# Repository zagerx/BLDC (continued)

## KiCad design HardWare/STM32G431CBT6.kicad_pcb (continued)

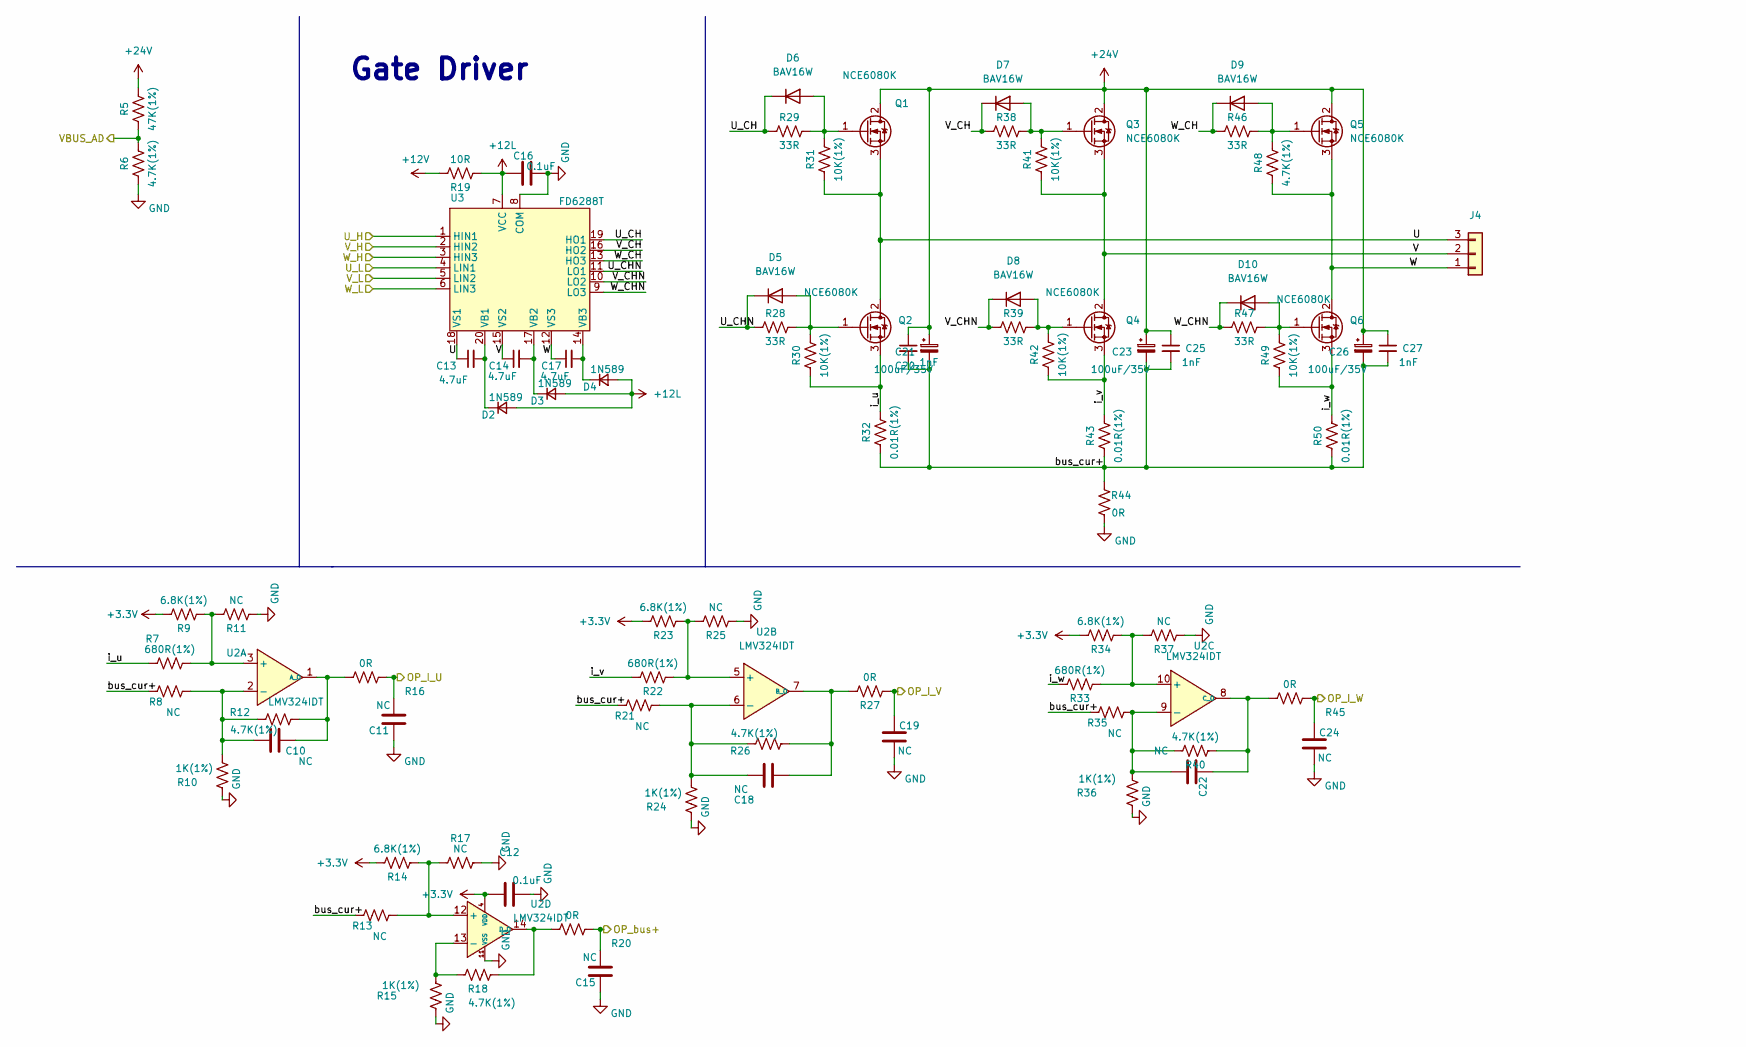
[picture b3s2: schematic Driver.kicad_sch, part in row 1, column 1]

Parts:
C10, C11, C15, C18, C19, C22, C24: NC; C_0603_1608Metric
C12, C16: 0.1uF; C_0603_1608Metric
C13, C14, C17: 4.7uF; C_0805_2012Metric
C20, C25, C27: 1nF; C_0603_1608Metric
C21, C23, C26: 100uF/35V; CP_Radial_D6.3mm_P2.50mm
D2, D3, D4: 1N589; D_SOD-123
D5, D6, D7, D8, D9, D10: BAV16W; D_SOD-123
J4: Conn_01x03; TerminalBlock_bornier-3_P5.08mm
Q1, Q2, Q3, Q4, Q5, Q6: NCE6080K; TO-252-2
R5: 47K(1%); R_0603_1608Metric
R6, R12, R18, R26, R40, R48: 4.7K(1%); R_0603_1608Metric
R7, R22, R33: 680R(1%); R_0603_1608Metric
R8, R11, R13, R17, R21, R25, R35, R37: NC; R_0603_1608Metric
R9, R14, R23, R34: 6.8K(1%); R_0603_1608Metric
R10, R15, R24, R36: 1K(1%); R_0603_1608Metric
R16, R20, R27, R45: 0R; R_0603_1608Metric
R19: 10R; R_0603_1608Metric
R28, R29, R38, R39, R46, R47: 33R; R_0603_1608Metric
R30, R31, R41, R42, R49: 10K(1%); R_0603_1608Metric
R32, R43, R50: 0.01R(1%); R_2512_6332Metric
R44: 0R; R_2512_6332Metric
U2: LMV324IDT; SO-14_3.9x8.65mm_P1.27mm
U3: FD6288T; TSSOP-20_4.4x6.5mm_P0.65mm

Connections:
+3V3: C12.2, R9.1, R14.1, R23.1, R34.1, U2.4 (VDD); also elsewhere on the board
+12L: C16.2, D2.2 (A), D3.2 (A), D4.2 (A), R19.2, U3.7 (VCC)
+12V: R19.1; also elsewhere on the board
+24V: C20.1, C21.1, C23.1, C25.1, C26.1, C27.1, Q1.2 (D), Q3.2 (D), Q5.2 (D), R5.1; also elsewhere on the board
/Driver/U: C13.1, J4.3, Q1.3 (S), Q2.2 (D), R31.2, U3.18 (VS1)
/Driver/U_CH: D6.1 (K), R29.2, U3.19 (HO1)
/Driver/U_CHN: D5.1 (K), R28.2, U3.11 (LO1)
/Driver/V: C14.1, J4.2, Q3.3 (S), Q4.2 (D), R41.2, U3.15 (VS2)
/Driver/V_CH: D7.1 (K), R38.2, U3.16 (HO2)
/Driver/V_CHN: D8.1 (K), R39.2, U3.10 (LO2)
/Driver/W: C17.1, J4.1, Q5.3 (S), Q6.2 (D), R48.2, U3.12 (VS3)
/Driver/W_CH: D9.1 (K), R46.2, U3.13 (HO3)
/Driver/W_CHN: D10.1 (K), R47.2, U3.9 (LO3)
/Driver/bus_cur+: C20.2, C21.2, C23.2, C25.2, C26.2, C27.2, R8.1, R13.1, R21.1, R32.2, R35.1, R43.2, R44.1, R50.2
/Driver/i_u: Q2.3 (S), R7.1, R30.2, R32.1
/Driver/i_v: Q4.3 (S), R22.1, R42.2, R43.1
/Driver/i_w: Q6.3 (S), R33.1, R49.2, R50.1
/OP_I_U: C11.2, R16.2; also elsewhere on the board
/OP_I_V: C19.1, R27.2; also elsewhere on the board
/OP_I_W: C24.1, R45.2; also elsewhere on the board
/OP_bus+: C15.2, R20.2; also elsewhere on the board
/TIM1_CH1: U3.1 (HIN1); also elsewhere on the board
/TIM1_CH1N: U3.4 (LIN1); also elsewhere on the board
/TIM1_CH2: U3.2 (HIN2); also elsewhere on the board
/TIM1_CH2N: U3.5 (LIN2); also elsewhere on the board
/TIM1_CH3: U3.3 (HIN3); also elsewhere on the board
/TIM1_CH3N: U3.6 (LIN3); also elsewhere on the board
/VBUS_AD: R5.2, R6.1; also elsewhere on the board
GND: C11.1, C12.1, C15.1, C16.1, C19.2, C24.2, R6.2, R10.1, R11.2, R15.1, R17.2, R24.1, R25.2, R36.1, R37.2, R44.2, U2.11 (VSS), U3.8 (COM); also elsewhere on the board
unnamed: C10.1, R8.2, R10.2, R12.1, U2.2 (-)
unnamed: C10.2, R12.2, R16.1, U2.1 (A_O)
unnamed: C13.2, D2.1 (K), U3.20 (VB1)
unnamed: C14.2, D3.1 (K), U3.17 (VB2)
unnamed: C17.2, D4.1 (K), U3.14 (VB3)
unnamed: C18.1, R26.2, R27.1, U2.7 (B_O)
unnamed: C18.2, R21.2, R24.2, R26.1, U2.6 (-)
unnamed: C22.1, R40.2, R45.1, U2.8 (C_O)
unnamed: C22.2, R35.2, R36.2, R40.1, U2.9 (-)
unnamed: D5.2 (A), Q2.1 (G), R28.1, R30.1
unnamed: D6.2 (A), Q1.1 (G), R29.1, R31.1
unnamed: D7.2 (A), Q3.1 (G), R38.1, R41.1
unnamed: D8.2 (A), Q4.1 (G), R39.1, R42.1
unnamed: D9.2 (A), Q5.1 (G), R46.1, R48.1
unnamed: D10.2 (A), Q6.1 (G), R47.1, R49.1
unnamed: R7.2, R9.2, R11.1, U2.3 (+)
unnamed: R13.2, R14.2, R17.1, U2.12 (+)
unnamed: R15.2, R18.1, U2.13 (-)
unnamed: R18.2, R20.1, U2.14 (D_O)
unnamed: R22.2, R23.2, R25.1, U2.5 (+)
unnamed: R33.2, R34.2, R37.1, U2.10 (+)

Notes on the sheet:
Gate Driver

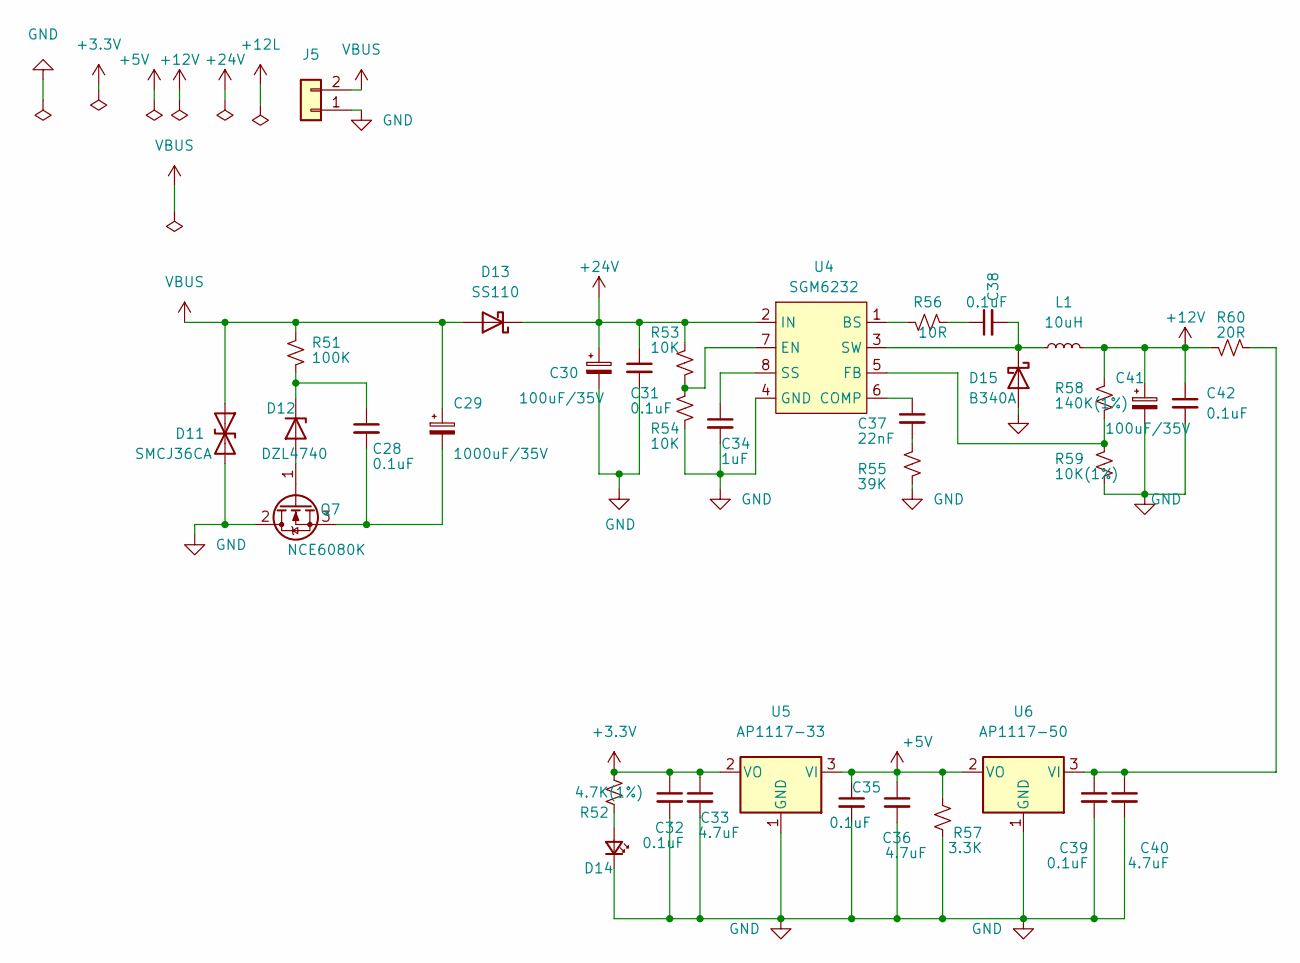
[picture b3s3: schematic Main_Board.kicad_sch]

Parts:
C28, C31, C32, C35, C38, C39, C42: 0.1uF; C_0603_1608Metric
C29: 1000uF/35V; CP_Radial_D12.5mm_P5.00mm
C30, C41: 100uF/35V; CP_Radial_D6.3mm_P2.50mm
C33, C36, C40: 4.7uF; C_0805_2012Metric
C34: 1uF; C_0603_1608Metric
C37: 22nF; C_0603_1608Metric
D11: SMCJ36CA; D_SMC
D12: DZL4740; D_SOD-123F
D13: SS110; D_SMA
D14: LED_Red; D_0603_1608Metric_Pad1.05x0.95mm_HandSolder
D15: B340A; D_SMA
J5: Conn_01x02; TerminalBlock_bornier-2_P5.08mm
L1: 10uH; L_Abracon_ASPI-0630LR
Q7: NCE6080K; TO-252-2
R51: 100K; R_0603_1608Metric
R52: 4.7K(1%); R_0603_1608Metric
R53, R54: 10K; R_0603_1608Metric
R55: 39K; R_0603_1608Metric
R56: 10R; R_0603_1608Metric
R57: 3.3K; R_0603_1608Metric
R58: 140K(1%); R_0603_1608Metric
R59: 10K(1%); R_0603_1608Metric
R60: 20R; R_0603_1608Metric
U4: SGM6232; SOIC-8_3.9x4.9mm_P1.27mm
U5: AP1117-33; SOT-223-3_TabPin2
U6: AP1117-50; SOT-223-3_TabPin2

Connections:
+3V3: C32.1, C33.1, R52.2, U5.2 (VO); also elsewhere on the board
+5V: C35.1, C36.1, R57.1, U5.3 (VI), U6.2 (VO)
+12V: C41.1, C42.1, L1.2, R58.1, R60.1; also elsewhere on the board
+24V: C30.1, C31.1, D13.1 (K), R53.1, U4.2 (IN); also elsewhere on the board
GND: C30.2, C31.2, C32.2, C33.2, C34.2, C35.2, C36.2, C39.2, C40.2, C41.2, C42.2, D11.2 (A2), D14.1 (K), D15.2 (A), J5.1, Q7.2 (D), R54.2, R55.2, R57.2, R59.2, U4.4 (GND), U5.1 (GND), U6.1 (GND); also elsewhere on the board
unnamed: C28.1, D12.1 (K), R51.2
unnamed: C28.2, C29.2, Q7.3 (S)
unnamed: C34.1, U4.8 (SS)
unnamed: C37.1, U4.6 (COMP)
unnamed: C37.2, R55.1
unnamed: C38.1, R56.2
unnamed: C38.2, D15.1 (K), L1.1, U4.3 (SW)
unnamed: C39.1, C40.1, R60.2, U6.3 (VI)
unnamed: D12.2 (A), Q7.1 (G)
unnamed: D14.2 (A), R52.1
unnamed: R53.2, R54.1, U4.7 (EN)
unnamed: R56.1, U4.1 (BS)
unnamed: R58.2, R59.1, U4.5 (FB)
VBUS: C29.1, D11.1 (A1), D13.2 (A), J5.2, R51.1

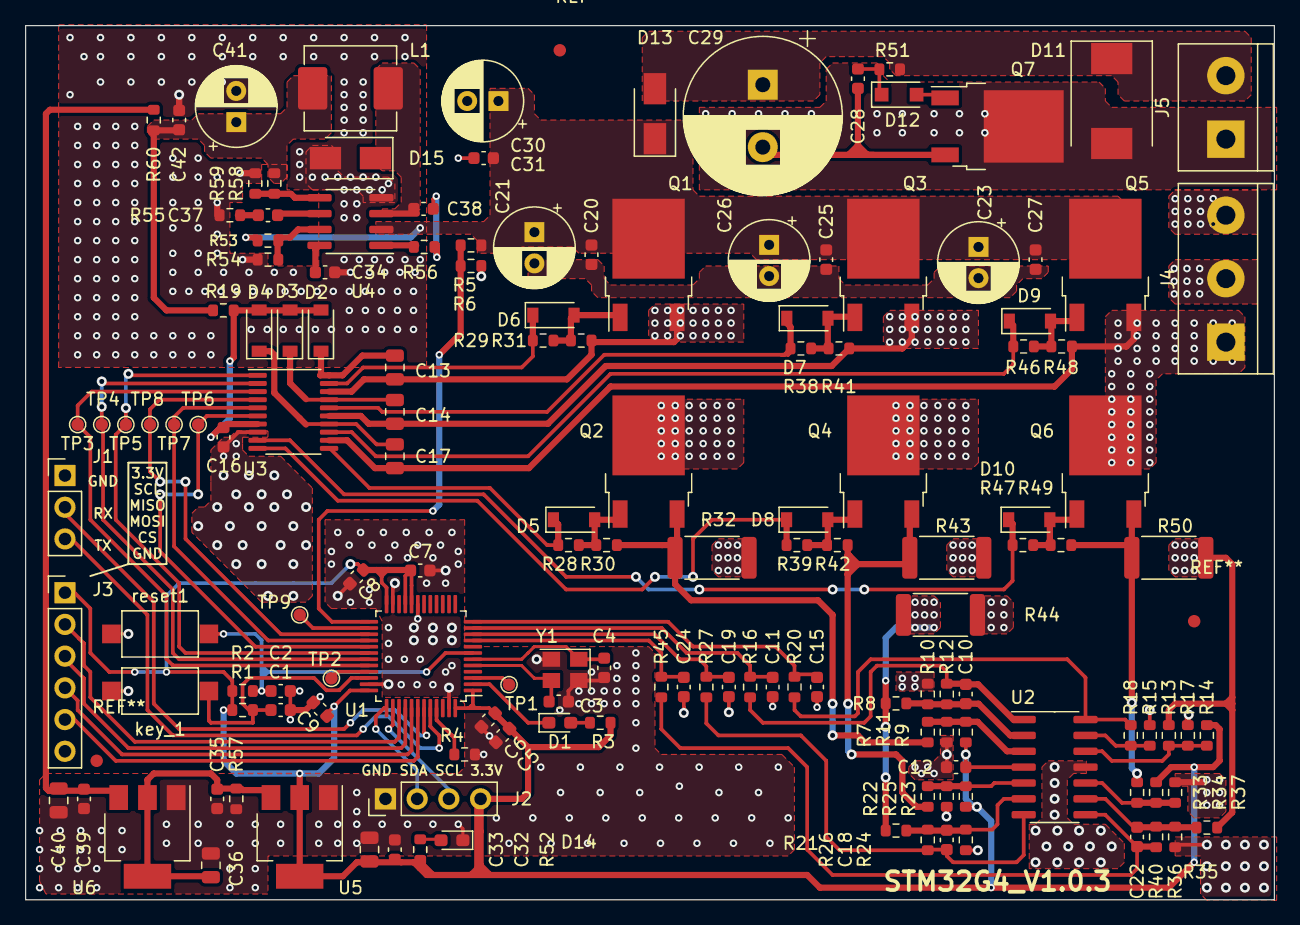
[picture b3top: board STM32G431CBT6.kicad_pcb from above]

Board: 2 copper layers, 100.0 x 70.0 mm, 148 parts (0 on the bottom side), 83 nets.

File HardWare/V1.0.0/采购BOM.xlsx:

Designator | Footprint | Quantity | Value | Price
C21, C23, C26, C30, C41 | CP_Radial_D6.3mm_P2.50mm | 5 | 100uF/35V | 0.08 | 0.4 |  |  |  | 优信
C29 | CP_Radial_D12.5mm_P5.00mm | 1 | 1000uF/35V | 0.5 | 0.5 |  |  |  | 优信
D10, D5, D6, D7, D8, D9 | D_SOD-123 | 6 | BAV16W | 0.12 | 0.72 |  |  |  | 优信
D11 | D_SMC | 1 | SMCJ36CA | 0 | 0
D12 | D_SOD-123F | 1 | DZL4740 | 0.3 | 0.3 |  |  |  | 立创
D13 | D_SMA | 1 | SS110 | 0.14000000000000001 | 0.14000000000000001
D15 | D_SMA | 1 | B340A | 0.22 | 0.22
D2, D3, D4 | D_SOD-123 | 3 | 1N589 | 6.4000000000000001E-2 | 0.192 |  |  |  | Risym
L1 | L_Abracon_ASPI-0630LR | 1 | 10uH | 0.16 | 0.16
Q1, Q2, Q3, Q4, Q5, Q6, Q7 | TO-252-2 | 7 | NCE6080K | 0.99 | 6.93 | NCE6050K替代 |  | 2.1
R32, R43, R50 | 2512 | 3 | 0.01R(1%) | 0.3 | 0.89999999999999991
R44 | 2512 | 1 | 0R | 0.15 | 0.15
U1 | LQFP-48_7x7mm_P0.5mm | 1 | STM32G431C8T6 | 13.8 | 13.8
U2 | SO-14_3.9x8.65mm_P1.27mm | 1 | LMV324IDT | 2 | 2 | TI替代 |  | 1.25
U3 | TSSOP-20_4.4x6.5mm_P0.65mm | 1 | FD6288T | 3.2 | 3.2 | EG2134替代 |  | 1.8
U4 | SOIC-8_3.9x4.9mm_P1.27mm | 1 | SGM6232 | 0.8 | 0.8
U5 | SOT-223-3_TabPin2 | 1 | AMS1117-33 | 0.4 | 0.4
U6 | SOT-223-3_TabPin2 | 1 | AMS1117-50 | 0.4 | 0.4
Y1 | Crystal_SMD_3225-4Pin_3.2x2.5mm | 1 | 32MHZ | 0.19 | 0.19
key_1, reset1 | SW_SPST_CK_RS282G05A3 | 2 | SW_Push | 0.1 | 0.2
J4 | TerminalBlock_bornier-3_P5.08mm | 1 | Conn_01x03 | 0.5 | 0.5
J5 | TerminalBlock_bornier-2_P5.08mm | 1 | Conn_01x02 | 0.3 | 0.3
 |  |  |  |  | 32.402000000000001

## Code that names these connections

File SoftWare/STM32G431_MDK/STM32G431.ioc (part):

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Mcu.Name=STM32G431C(6-8-B)Tx
Mcu.Package=LQFP48
Mcu.UserName=STM32G431C8Tx
PA1.Mode=IN2-Single-Ended
PA1.Signal=ADC1_IN2
PA10.Signal=S_TIM1_CH3
PA11.Signal=S_TIM1_CH4
PA12.GPIOParameters=GPIO_Label
PA12.GPIO_Label=KEY_01
PA12.Signal=GPXTI12
PA13.Mode=Serial_Wire
PA13.Signal=SYS_JTMS-SWDIO
PA14.Mode=Serial_Wire
PA14.Signal=SYS_JTCK-SWCLK
PA15.GPIOParameters=GPIO_Label
PA15.GPIO_Label=MT68XX_CSN
PA15.Signal=GPIO_Output
PA2.Mode=IN3-Single-Ended
PA2.Signal=ADC1_IN3
PA3.Mode=IN4-Single-Ended
PA3.Signal=ADC1_IN4
PA8.Signal=S_TIM1_CH1
PA9.Signal=S_TIM1_CH2
PB0.Mode=IN15-Single-Ended
PB0.Signal=ADC1_IN15
PB1.Mode=IN12-Single-Ended
PB1.Signal=ADC1_IN12
PB13.Mode=PWM Generation1 CH1 CH1N
PB13.Signal=TIM1_CH1N
PB14.Mode=PWM Generation2 CH2 CH2N
PB14.Signal=TIM1_CH2N
PB15.Mode=PWM Generation3 CH3 CH3N
PB15.Signal=TIM1_CH3N
PB3.Mode=Full_Duplex_Master
PB3.Signal=SPI1_SCK
PB4.Mode=Full_Duplex_Master
PB4.Signal=SPI1_MISO
PB5.Mode=Full_Duplex_Master
PB5.Signal=SPI1_MOSI
PB6.Mode=Asynchronous
PB6.Signal=USART1_TX
PB7.Mode=Asynchronous
PB7.Signal=USART1_RX
PC13.GPIOParameters=GPIO_Label
PC13.GPIO_Label=LED_01
PC13.Signal=GPIO_Output
PF0-OSC_IN.Mode=HSE-External-Oscillator
PF0-OSC_IN.Signal=RCC_OSC_IN
PF1-OSC_OUT.Mode=HSE-External-Oscillator
PF1-OSC_OUT.Signal=RCC_OSC_OUT
RCC.HSE_VALUE=32000000
RCC.SYSCLKFreq_VALUE=84000000
RCC.SYSCLKSource=RCC_SYSCLKSOURCE_PLLCLK
board=custom

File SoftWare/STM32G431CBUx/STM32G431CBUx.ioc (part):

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Mcu.Name=STM32G431C(6-8-B)Ux
Mcu.Package=UFQFPN48
Mcu.UserName=STM32G431CBUx
PA0.Mode=IN1-Single-Ended
PA0.Signal=ADC1_IN1
PA1.Mode=Standalone
PA1.Signal=OPAMP1_VINP
PA10.Signal=S_TIM1_CH3
PA13.Mode=Serial_Wire
PA13.Signal=SYS_JTMS-SWDIO
PA14.Mode=Serial_Wire
PA14.Signal=SYS_JTCK-SWCLK
PA2.Signal=SharedAnalog_PA2
PA3.Mode=Standalone
PA3.Signal=OPAMP1_VINM
PA4.GPIOParameters=GPIO_Label
PA4.GPIO_Label=AS5047_CS
PA4.Signal=GPIO_Output
PA5.Mode=Standalone
PA5.Signal=OPAMP2_VINM
PA6.Signal=SharedAnalog_PA6
PA7.Mode=Standalone
PA7.Signal=OPAMP2_VINP
PA8.Signal=S_TIM1_CH1
PA9.Signal=S_TIM1_CH2
PB0.Mode=Standalone
PB0.Signal=OPAMP3_VINP
PB1.Signal=SharedAnalog_PB1
PB10.Mode=Asynchronous
PB10.Signal=USART3_TX
PB11.Mode=Asynchronous
PB11.Signal=USART3_RX
PB12.Mode=IN11-Single-Ended
PB12.Signal=ADC1_IN11
PB13.Mode=PWM Generation1 CH1 CH1N
PB13.Signal=TIM1_CH1N
PB14.Mode=PWM Generation2 CH2 CH2N
PB14.Signal=TIM1_CH2N
PB15.Mode=PWM Generation3 CH3 CH3N
PB15.Signal=TIM1_CH3N
PB2.Mode=Standalone
PB2.Signal=OPAMP3_VINM
PB3.Mode=Full_Duplex_Master
PB3.Signal=SPI1_SCK
PB4.Mode=Full_Duplex_Master
PB4.Signal=SPI1_MISO
PB5.Mode=Full_Duplex_Master
PB5.Signal=SPI1_MOSI
PB6.Signal=S_TIM4_CH1
PB7.Signal=S_TIM4_CH2
PB8-BOOT0.Signal=S_TIM4_CH3
PC4.GPIOParameters=GPIO_Label
PC4.GPIO_Label=LED01
PC4.Signal=GPIO_Output
PC6.GPIOParameters=GPIO_Label
PC6.GPIO_Label=LED02
PC6.Signal=GPIO_Output
PF0-OSC_IN.Mode=HSE-External-Oscillator
PF0-OSC_IN.Signal=RCC_OSC_IN
PF1-OSC_OUT.Mode=HSE-External-Oscillator
PF1-OSC_OUT.Signal=RCC_OSC_OUT
RCC.HSE_VALUE=24000000
RCC.SYSCLKFreq_VALUE=160000000
RCC.SYSCLKSource=RCC_SYSCLKSOURCE_PLLCLK
board=custom

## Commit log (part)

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2024-03-04 20240305 00:07
2024-03-05 20240305 18:08
2024-03-05 20240306 00:46
2024-03-06 20240306 19:20
2024-03-06 20240307 01:01
2024-03-07 20240307 19:21
2024-03-07 1、重要更新！！！G431_GCC版本完成电流环闭环。 2、:20240308 01:23
2024-03-08 20240308 18:58
2024-03-10 20240311 00:19
2024-03-11 20240311 19:32
2024-03-11 20240312 01:25
2024-03-12 20240312 19:30
2024-03-12 20240313 01:44
2024-03-13 20240313 19:03
2024-03-13 20240314 01:44
2024-03-17 20240318 01:43
2024-03-20 mcbv06_hallcoder opt
2024-03-20 20240320 19:03
2024-03-20 20240321 01:28
2024-03-21 20240321 19:17
2024-03-23 20240323 19:17
2024-03-24 20240325 02:25
2024-03-25 20240326 01:38
2024-03-30 20240330 15:37
2024-03-30 20240331 00:54
2024-03-31 20240401 00:44
2024-04-26 20240427
2024-04-27 20240428 00:45
2024-05-05 f405 增加pll角度功能
2024-05-06 20240507 01:15
2024-05-07 20240507 22:59
2024-05-08 20240508 14:26
2024-05-08 20240508 19:52
2024-05-08 f405 pwm:16khz adc normal
2024-05-09 20240509 15:50
2024-05-09 20250509 19:41
2024-05-10 20240510 17:25
2024-05-14 20240515 01:54 编码器未测试
2024-05-19 20240519 Odriver 移植通过
2024-05-20 20240521 02:10 对_board.c文件进行拆分
2024-05-21 20240521 修改了一些文件名
2024-05-21 20240521 19:28
2024-05-21 重要更新！移除_board.c文件,as5047.c优化
2024-05-22 20240522 21:48
2024-05-22 重要节点！20240523 01:11
2024-05-23 20240523 10:35
2024-05-23 20240523 18:48
2024-05-23 20240523 23:24
2024-05-23 20240524 01:38 G4 PWM正常
2024-05-24 g4 adc采样正常
2024-05-25 G314版本电流闭环初步OK，还需进一步优化
2024-05-25 G431增加母线电压检测功能，保护逻辑待完善
2024-05-26 F405电流检测有问题
2024-05-26 F405/G431测试通过。G431的Iq反向
2024-05-27 20240527 19:47
2024-05-27 重要更新！！！G431电流闭环！！！
2024-05-28 20240529 增加AS5047硬件原理图
2024-05-28 1、优化一部分代码，删除无用的代码 2、F405未测试
2024-05-29 增加AS5047Board机械图纸
2024-05-30 修改硬件版本V02
2024-06-02 20240603 HardWare优化
2024-06-03 20240604 优化硬件原理图及封装
2024-06-04 20240604 13:27 优化执行器模块
2024-06-04 20240604 18:48 执行模块测试通过，ADC采样通过，电机TIM配置还需优化
2024-06-04 20240605 01:28 完成硬件初步布局
2024-06-05 20240606 01:01 硬件:电源布局完成
2024-06-06 20240607 01:44 硬件初步布局已完成
2024-06-07 20240608 增加Can电路，优化整体布局
2024-06-10 20240610 硬件布局完成95%，软件增加速度环
2024-06-14 20240615 PCB绘制结束
2024-06-16 20240617 00:44，增加母线电压检测功能
2024-06-19 20240619 上位机修改，增加pid调试界面
2024-06-19 20240620 增加FSM模块，待完善
2024-06-20 20240621 00:52优化交互模式
2024-06-23 20240623 优化交互模式
2024-06-26 Add initmodule
2024-06-29 sensor module update
2024-06-29 Add MSG LIST
2024-07-02 修改了电机控制模块
2024-07-02 增加多工程makefile文件
2024-07-03 优化传感器模块，优化系统模块
2024-07-04 增加Cmback_trace模块
2024-07-08 修改protocoltransmit.h文件
2024-07-10 修改QT Project
2024-07-11 20240712优化QT工程
2024-07-14 20240715 优化QT工程
2024-07-15 20240715 修改H7工程
2024-07-15 20240715 修改H7部分代码
2024-07-15 完成上位机QT工程，串口“发送功能”框架
2024-07-16 20240716 修改H7
2024-07-23 添加embeddedtool.md文件
2024-07-25 20240725
2024-07-25 protocol init commit
2024-07-29 1、正常响应上位机指令 正常模式/电机启动/电机停止 2、协议重构完成50%
2024-08-07 1、电流环频率调整为10KHZ
2024-08-07 1、增加程序运行状态指示灯
2024-08-08 1、开发协议重发功能，进度40% 2、通用链表部分待完善
2024-08-10 1、协议重发功能，完成60%。
2024-08-10 1、协议重发功能完成80%
2024-08-10 1、CubeMx取消main函数生成
2024-08-10 1、优化一些文件/函数的命名
2024-08-14 1、QT增加QCharts模块
2024-08-17 1、增加key_Moudle,TODO
2024-08-18 1、QT接收发送完成80%，TODO
2024-08-18 QT完成90%,charts更新待完善，TODO
2024-08-19 1、MCOM功能优化，relase版本
2024-08-19 1、MCOM工程v1.0.0版本
2024-08-20 temp
2024-08-26 1、G4_MCBV06工程修改
2024-08-26 修改MCB_V06
2024-08-28 G473 flash test...pass
2024-08-30 1、STM32G4_MCBV06 2、增加LPUART打印功能 3、增加make stlinkdown命令
2024-08-30 1、G4_MCBV06修改，TODO
2024-08-30 1、F405工程，增加电机控制相关代码
2024-08-31 1、F405修改，TODO
2024-09-02 F405 协议指令正常 电流采集正常，角度获取正常
2024-09-03 增加一些说明文档
2024-09-03 1、MotorCtrl模块，增加通用的协议发送函数(待测试) 2、补充相关说明文档
2024-09-03 1、MotorCtrl模块增加void mc_encoderopenlooptest(float *iabc,float omega)函数 2、F405,编码器开环测试通过,IQ,ID正确跟随
2024-09-03 1、优化Flash模块，分层处理。待测试
2024-09-04 1、优化Flash模块分层，TODO
2024-09-04 1、电机协议增加操作PID指令，TODO 2、F405增加软复位功能
2024-09-04 1、F405,PID调试流程通过，代码/整理需整理 2、id无法响应负数
2024-09-06 1、修改PID无法输出负值
2024-09-06 1、速度/电流符号符号整体符合预期 2、各个参数需优化
2024-09-07 1、F405 优化代码 2、删除力矩模式,h.c/.h 3、优化电流环/速度环/编码器接口 4、删除正常模式.c/.h
2024-09-07 1、修改电流模式,速度模式.c/.h文件名 2、取消Debug模式，改为速度模式
2024-09-07 1、修改了一些头文件的包含路径
2024-09-07 1、新增motor_normal.c/.h模式 2、修改电机状态机的调用，实现速度模式切换正常模式时，自动停止电机
2024-09-07 1、修改motorctrl_cfg.c的接口文件 2、修改角度接口文件 3、修改QT3、修改QT,：显示速度功能,显示速度功能
2024-09-08 1、BLDC:v1.0.0版本
2024-09-09 1、BLDC:v1.0.1版本
2024-09-10 1、BLDC:v1.0.2版本
2024-09-13 1、BLDC:v1.0.2_1版本
2024-09-17 1、对速度进行低通滤波
2024-09-18 1、增加位置模式。TODO
2024-09-19 BLDC:v1.03版本
2024-09-21 1、串口波特率设置2000000 2、波形图使用Qcustomplot绘制（速度显示正常）
2024-09-21 1、波形图新增加一组数据
2024-09-23 1、QT修改串口接收缓冲
2024-09-24 1、CustomPlot增加子图模块
2024-09-25 1、优化代码风格
2024-09-25 1、QT波形图优化
2024-09-26 20240926t
2024-09-29 1、SPI_Bus抽象，TODO
2024-09-29 1、优化SPI/AS5047分层
2024-10-01 1、BLDC:v1.0.4版本
2024-10-09 1、增加SMO观测器文档 2、构建基本框架(代码参考TI)
2024-10-10 1、优化Hardware分层 2、测试H7工程IAN226,外设正常
2024-10-10 1、速度模式、反转模式下，smo可正常追踪角度(TODO)
2024-10-10 1、H7工程IAN226分层优化
2024-10-11 1、H7工程 INA226和tca9539共用I2C接口，测试通过 2、底层I2C仍需优化
2024-10-12 1、增加Spi_Bus模块
2024-10-14 v1.0.0
2024-10-14 v1.0.1
2024-10-15 1、mcb_v06增加LPUART功能
2024-10-16 1、MCB_V06增加电机控制模块,电机原地转动
2024-10-16 BLDC:v1.0.4_1
2024-10-17 MCB_V06 自开环正常，电流不稳定(一直增长)，待优化
2024-10-17 MCB_V06:增加死区时间，电机正常转动，仍待优化
2024-10-17 MCB_V06 增加霍尔编码器相关内容
2024-10-20 1、公共模块增加hall sensor待测试
2024-10-20 1、优化QT部分
2024-10-21 1、优化Hall_sensor部分，待测试
2024-10-21 1、优化QT部分，新建数据处理线程，正常运行，功能待优化
2024-10-21 1、优化hall_sensor模块及mc_encoder模块。待测试
2024-10-22 1、MCB_V06优化Hall_sensor
2024-10-22 1、MCB_V06调整hall部分
2024-10-23 MCB_V06 优化Hall模块
2024-10-23 1、新增STM32G431CBUx工程
2024-10-24 1、STM32G431CBUx 工程增加电机控制模块 2、串口DMA发送有问题，待优化
2024-10-26 1、STM32G431CBUx 工程增加电机控制模块
2024-10-26 1、G431CBUx工程配置电位器ADC
2024-10-26 1、STM32G431CBUx工程配置三相电流运放通道，电流采集通道
2024-10-26 1、STM32G431CBUx配置运放，ADC，Voft
2024-10-27 1、STM32G431CBUx工程配置定时器，定时器自开环工程正常
2024-10-28 1、MCB_V06优化HallSensor部分
2024-10-28 1、MCBV06优化HALLSENSOR模块 2、Q轴强拖模式下，可以追踪到自给角度
2024-10-28 1、STM32G431CBUx 编码器自开环，正向转动正常。 2、反向转动卡死，待优化
2024-10-29 1、STM32G431CBUx编码器自开环正常 2、反转效果更好，不易堵转 3、正转待优化
2024-10-30 1、优化HallSensor 2、MCBV06编码器自开环正常(有抖动，待解决)
2024-10-30 1、优化HALLSENSOR中
2024-10-31 1、MCBV06 霍尔功能优化中
2024-11-01 1、MCBV06修改hall方向 2、Uq>0，表现不好。Uq<0,表现正常 3、id,iq正常
2024-11-02 1、STM32G431CBUx工程，HallSensor编码器开环通过 2、正反转工况相同
2024-11-02 1、STM32G431CBUx优化中
2024-11-03 1、优化Hall模块及mc_encoder模块
2024-11-03 1、代码优化 2、STM32G431CBUx,编码器开环正常 3、MCB_V06，G431-GCC工程编译通过
2024-11-03 1、修改BLDCMotor模块 2、G431_GCC工程待验证
2024-11-04 1、MCBV06工程，编码器开环正常(Uq<0.15f),当Uq>0.15无法正确追踪角度
2024-11-04 1、HallSensor增加PLL模块，可正常追踪角度 2、Uq值过大，电机抖动及停机。未解决 3、PLL模块，PI参数仍需优化
2024-11-04 1、STM32G431CBux工程，PLL锁相环功能正常
2024-11-05 1、MCBV06完善关于Hallsensor的说明
2024-11-05 1、QT工程增加说明文档
2024-11-05 1、QT工程，优化按键部分
2024-11-06 1、MCBV06优化PLL参数，电机启动偶尔失败，待优化 2、修改采样硬件参数
2024-11-06 20241107
2024-11-07 1、重构MotorCtrl模块 2、优化中
2024-11-08 1、MCBV06 增加float打印
2024-11-08 1、BLDCMotor模块重构中
2024-11-09 1、STM32G431CBUx完成速度环调试 2、Iq被限制，待优化
2024-11-10 1、STM32G431CBux工程，速度环调试OK 2、可响应目标速度100到500之间。 3、电流环限制力矩还需优化，未达到最大出力
2024-11-11 1、修改电机控制中的读取Flash方法，对其进行隔离
2024-11-11 1、H7工程，串口配置通过
2024-11-11 1、新建ProtocolV2文件夹
2024-11-12 1、MCB_V06增加ABZ编码器功能
2024-11-12 1、MCBV06优化ABZ编码器，速度环测试通过 2、角度稳定性不高，待优化
2024-11-12 1、增加对PLL的速度明显滤波,效果不明显
2024-11-13 1、拆分motor_init函数 2、优化hall启动代码
2024-11-14 temp2
2024-11-14 1、修改MotorCtrl模块，MCBV06待优化
2024-11-15 1、H7工程优化，通信正常，电机转动正常 2、ABZ信号需重新修改引脚
2024-11-15 1、H7编码器开环测试OK
2024-11-15 1、H7可正常工作，电流采样需要优化
2024-11-15 1、STM32G431CBUx工程，Tim4开启Hall捕获模式
2024-11-17 1、STM32G431CBUx优化基准角
2024-11-17 1、增加Encoder_openloop_mode
2024-11-17 1、STM32G431CBUx，编码器自开环测试通过，反向切换有抖动，待优化
2024-11-18 1、优化H7，编码器自开环正常，电流采样待解决
2024-11-19 1、优化abs_sensor模块
2024-11-19 1、优化hall_sensor模块，STM32G431CB工程测试通过
2024-11-20 1、STM32G431CBUx，速度环测试通过 2、细节待优化
2024-11-20 1、增加T型加速
2024-11-21 1、MotorCtrl增加匀加减速功能,待测试
2024-11-21 1、优化Hall注册函数
2024-11-22 1、增加宏相关文件夹
2024-11-24 1、增加S型加减速文档
2024-11-25 1、优化accdece_speed.c20241125
2024-11-26 1、直线插补算法完成
2024-11-26 1、增加S型路径/速度算法 2、下降阶段逻辑待优化
2024-11-27 1、MCB_V06 编码器开环OK，反向需优化
2024-12-04 1、优化S型加减速算法
2024-12-05 1、S型插补算法第一阶段完成 2、能够进行固定值插补
2024-12-06 1、S型插补算法优化中 2、完成自动推导Ja功能
2024-12-06 1、S型插补算法V1.0.1
2024-12-10 1、增加UAVCAN文档
2024-12-16 1、重龙适配750W电机，测试通过
2024-12-17 1、调整G4_MCB的HALL_ABZ模式
2024-12-18 1、基于H7工程优化encoder模块，测试通过
2024-12-18 1、优化Motor模块
2024-12-19 1、优化Motor下Encoder模块 2、优化hall模块 3、H7,MCB_V06测试通过
2024-12-19 1、H7工程750W电机，编码器开环测试通过
2024-12-24 1、开发直线插补算法
2024-12-25 1、优化encoder模块
2024-12-27 1、优化直线插补算法
2024-12-30 1、H7开启随机数功能 2、优化测试函数
2024-12-30 1、直线规划模块，增加0速保持功能
2025-01-01 1、优化直线加速模块
2025-01-02 cbu6取消main函数
2025-01-03 1、优化motor_ctrl模块
2025-01-04 temp 增加一些注释
2025-01-04 增加一些注释2
2025-01-05 1、适配431_GCC工程，编码器开环OK
2025-01-10 优化Hall模块的纯hall模式
2025-01-12 优化HALL模块wq
2025-01-14 优化一些代码风格
2025-01-14 优化Hall模块，适配H7 适配超龙电机,重龙电机 编码器自开环通过
2025-01-15 temp3
2025-01-15 temp4
2025-01-16 1、优化模块设计 2、去除一些不必要的变量及函数定义
2025-01-17 配置TIM1的PWM功能
2025-01-17 增加ADC1功能，部分采样不到
2025-01-21 H7双电机工程 编码器开环测试通过 电机1无法正确采样，待优化
2025-01-23 优化svpwm.md文档
2025-01-24 mc_focmath.c优化svpwm测试函数 增加限幅功能
2025-02-06 增加103核心板工程
2025-02-06 f103工程增加串口打印功能
2025-02-12 ADC多重模式配置 可以自开环转动 电机1电流波形不完美 电机1，2的读取到的角度不完美
2025-02-13 双电机工程编码器开环正常 电流采样正常 编码器角度值待优化
2025-02-13 优化MotorCtrl模块
2025-02-14 优化H7工程的tim.c文件 编码器自开环正常，电流采样正常
2025-02-17 优化hall模块，提高启动成功率，90%
2025-02-28 H7工程适配Ubunt下载
2025-03-03 增加uavcan部分
2025-03-03 增加pyQT6部分代码
2025-03-04 增加uavcan的里程计绘图功能
2025-03-05 dsdl文件转.c.h
2025-03-05 H7转移到linux下,CubeMx重新生成代码
2025-03-05 H7增加ClassCan接收功能,sucessful
2025-03-05 H7移植uavcan,请求订阅功能正常(电机使能)
2025-03-05 can发送正常,uavcan解析错误,超过100队列溢出
2025-03-14 添加 UAVCAN 子模块
2025-03-14 增加MCOM子模块
2025-03-14 f103_fire增加串口发送心跳
2025-03-18 新建STMH723_GCC_LL工程
2025-03-19 TIM1正常发波
2025-03-20 tim8,tim1定时器同步,正常发波
2025-03-20 修改.gitignor文件
2025-03-20 H7 UAVCAN发送接收测试通过
2025-03-20 增加PortocolV4子模块
2025-03-21 优化uavcan接口部分代码风格
2025-03-21 H7_LL 增加ADC模块
2025-03-21 ADC多重模式 HAL库 运行正常
2025-03-25 ADC双重模式 可以触发
2025-03-28 ADC初始化使用HAL库 拉低任何一个通道,其他两个通道都会跟随大幅变化 数据必须左移三位才能接近正常值
2025-03-28 初始化使用HAL库,其余LL库
2025-03-28 HAL+LLL库
2025-04-08 增加里程计数据,上报间隔1000ms
2025-04-17 优化board_protocolInterface.c,增加对设置速度指令的响应
2025-04-17 增加订阅时间戳同步消息
2025-05-07 增加OperateRemoteDevice和SoftStop指令
2025-11-15 增加motorlib模块在G431CB工程
2025-11-15 生成cmake工程
2025-11-15 对STM32G431CB工程增加DSP库
2025-11-15 增加pp_ident模块
2025-11-16 增加SPI通信
2025-11-16 优化pp_ident模块
2025-11-17 优化pp_ident模块正常工作 极对数识别成功率99%
2025-11-17 增加电流偏置校准模块
2025-11-18 优化状态调度逻辑,待测试
2025-11-18 优化CmakeLists.txt,增加宏定义
2025-11-18 优化拆分校准模块
2025-11-18 增加编码器校准功能
2025-11-19 增加log模块
2025-11-19 优化motor_carible.c/.h文件
2025-11-19 增加开环调试状态
2025-11-19 完善feedback模块,待测试
2025-11-19 优化编码器校准模块
2025-11-19 编码器开环模式,测试通过
2025-11-20 优化电机校准模块
2025-11-20 优化电流校准模块
2025-11-20 优化motor_calib.c/.h模块
2025-11-20 优化feedback模块
2025-11-21 优化feedback,pp_ident模块
2025-11-21 优化电流模块
2025-11-22 修正tim死区时间
2025-11-22 使用Cube重新生成工程
2025-11-22 ADC配置为双重模式
2025-11-22 Eulre:v0.0.1,编码器开环,测试通过
2025-11-22 串口接收功能正常
2025-11-22 重构pid模块
2025-11-23 修复feedback模块零点偏移赋值错误
2025-11-23 tim.c增加PWM保护机制
2025-11-23 移除一些不必要的变量
2025-11-23 一组较好的电流环参数
2025-11-23 对电压做了归一化处理
2025-11-23 增加速度环,参数待调试
2025-11-24 增加调试PID的一些方法
2025-11-24 优化调试逻辑
2025-11-24 速度环KP/Ki调试
2025-11-25 feedback模块增加低通滤波功能
2025-11-25 优化参数解析
2025-11-25 优化函数名
2025-11-25 优化命令解析
2025-11-25 增加电阻电感校准模块，待测试
2025-11-25 修复feedback模块速度突变
2025-11-25 v0.0.9版本,速度环测试通过
2025-11-26 优化_encoder_calib.c
2025-12-09 优化状态机文件
2025-12-10 增加windows下的调试脚本
2025-12-10 增加查表法,待优化
2025-12-10 优化变量名,移除一些不必要的字段
2025-12-10 增加一些忽略文件
2025-12-12 增加一些测试文件
2025-12-14 优化S轨迹规划文件
2025-12-15 增加t型加减速代码
2025-12-15 t型加减速初步测试通过
2025-12-15 优化t型算法
2025-12-16 增加临时文件
2025-12-17 增加卡尔曼滤波模块
2025-12-17 得到一组较好的PI参数
2025-12-17 增加开环强拖函数
2025-12-18 优化lut校准部分
2025-12-19 临时增加文件
2025-12-20 提取配置参数,优化命名
2025-12-20 优化命名
2025-12-21 优化变量命名，优化数据结构
2025-12-24 优化校准模块,开发中
2025-12-25 继续优化校准模块
2025-12-25 编码器优化初步结束
2025-12-26 优化变量名及数据结构
2025-12-26 继续优化编码器校准模块
2025-12-27 配置cubemx,增加母线电压通道
2025-12-27 优化feedbakc currsmp inverter模块
2025-12-28 增加位置模式
2026-01-03 V0.9.0
